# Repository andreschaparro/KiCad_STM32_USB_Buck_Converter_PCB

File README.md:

# KiCad STM32 + USB + Buck Converter PCB Design and JLCPCB Assembly

## Links

- [Fabricante de PCB](https://jlcpcb.com/).
- [Componentes](https://jlcpcb.com/parts).
- [Microcontrolador STM32 F4](https://jlcpcb.com/partdetail/Stmicroelectronics-STM32F405RGT6/C15742).
- [Conversor Buck](https://jlcpcb.com/partdetail/Monolithic_PowerSystems-MP2359DJ_LFZ/C14259).
- [Protección ESD para el USB](https://jlcpcb.com/partdetail/Stmicroelectronics-USBLC62SC6/C7519).
- [Cristal 16Mhz](https://jlcpcb.com/partdetail/Yxc_CrystalOscillators-X322516MLB4SI/C13738).
- [Protección Polaridad Inversa](https://jlcpcb.com/partdetail/Alpha_OmegaSemicon-AO3401A/C15127).
- [Ferrite para Conversores Buck](https://jlcpcb.com/partdetail/Sunlord-GZ2012D601TF/C1017).
- [Diodo Schottky recomendado para Conversores Buck](https://jlcpcb.com/partdetail/mdd_microdiode_semiconductor-B5819W/C64885).
- [Inductor de potencia para Conversores Buck](https://jlcpcb.com/partdetail/Sunlord-MWSA0503S100MT/C408412).

❗Minimizar el uso de extended parts y usar las basic para minimizar el costo del PCB.

## STM32CubeIDE

📝En lo posible, colocar los buses de comunicación en distintos laterales del microcontrolador. Y si no se puede, colocarlos lo mas separados que se pueda dentro del mismo lateral.

❗En la imagen, se ve una mala ubicación para la USART1 porque queda muy cerca del USB_FS. Para solucionar el problema, utilizar la USART3 que esta en otro lateral.

## Opciones para interconectar VDD con VDDA

## Cortex Debug Connector (10-pins, 0.05")

## Apilado estándar de 4 capas de JLCPCB

## Reglas de diseño JLCPCB

[Fabricante de PCB](https://jlcpcb.com/capabilities/pcb-capabilities).

## Pasos para armar el Layout

📝Trabajar con una grilla de 1mm o 0,25mm.

❗Si hay restricciones mecánicas, primero dibujar el borde de la placa y posicionar agujeros de montaje.

1. Colocar el microcontrolador.
2. Separar los componentes en grupos funcionales.
3. Colocar los capacitores de desacople de 100n lo mas cerca posible del microcontrolador.
4. Colocar el filtro de conexión entre VDD y VDDA lo mas cerca posible del microcontrolador.
5. Colocar los capacitores de VCAP_1 y VCAP_2 lo mas cerca posible del microcontrolador.
6. Colocar el circuito del cristal lo mas cerca posible del microcontrolador.
7. Colocar el capacitor de desacople de 4u7 o 10u cerca del capacitor de 100n que está más alejado de la salida del regulador Buck.

📝Medir distancias con la regla.

8. Colocar elementos del BOOT0.
9. Colocar el led de status.
10. Colocar el conector USB (con su protección ESD lo más cerca posible).
11. Colocar el conector de la UART.
12. Colocar el conector I2C y sus resistencia (más cerca del host que del conector).
13. Colocar los conectores de Debug y +12V.
14. Colocar todos los componentes del circuito de alimentación dentro de un área pequeña.

📝Utilizar el layout sugerido en la hoja de datos del conversor Buck.
📝Si no hay layout sugerido, los componentes de la red de realimentación deben estar cerca del conversor Buck.
📝Si no hay layout sugerido, los componentes de la red de filtrado deben estar cercanos entre sí y del conversor Buck.
📝Si hubiese señales análogicas, deberían estar bastante separadas del área del conversor Buck.

15. Colocar leds indicadores de alimentación.
16. Colocar los agujeros de montaje.
17. Dibujar el borde de la placa.
18. Ajustar conectores y otros elementos utilizando la perspectiva 3D de KiCad.

❗JLCPCB no utiliza las capas F.Fab y B.Fab. Por lo que se puede, enviar la númeración de componetes al F.Fab para ahorrar espacio.

## Pasos para el ruteo

📝Un ancho de pista de 0,3mm es práctico para hacer conexiones directa con el microcontrolador.

1. Capacitores de desacople.
2. La pista de HSE_IN debe pasar por el medio del cristal.

📝Corregir la posición vertical del cristal manualmente.

3. Todas las conexiones del circuito del cristal deben realizarse en el top layer.
4. Las pistas I2C_SDA e I2C_SDL deben separarse al menos 2 a 3 veces su ancho, y lo mas cerca posible del microcontrolador para evitar Crosstalk.
5. Las pistas TX y RX de una USART deben separarse con el mismo criterio que las de I2C.
6. Las pistas de Debug son de baja frecuencia.

❗Las pistas de baja frecuencia se pueden pasar por el bottom layer mediante vías y deben ser lo mas cortas posibles.

7. Para las pistas del circuito de alimentación, se pueden utilizar zonas de cobre o pistas gruesas.

📝La herramienta de cálculo de KiCad permite estimar la corriente que puede circular por una pista.

8. Las pistas USB son un par diferencial con impedancia controlada de 90.

📝Utilizar la herramienta [JLCPCB Impedance Calculator](https://jlcpcb.com/pcb-impedance-calculator) no la de KiCad.

9. La pista de BOOT0 es de baja frecuencia.
10. Realizar las conexiones con los planos de GND y +3.3V con vías de 0,8mm/0,4mm.

❗Las vías deben colocarse lo mas cerca posible sin tocar los pads para minimizar la resistencia e inductancia parásita.

📝Puede que haga falta más de una vía en función de la corriente.

❗Para la conexión entre VDD y VDDA poner al menos 2 vías para minimizar la resistencia e inductancia parásita.

❗Conectar las vías a los pads con trazos cortos y anchos (0,5mm o más).

❗En el regulador Buck utilizar al menos 2 vías por pad. Excepto, en el inductor donde conviene que tenga al menos 4.

❗En el GND del USB poner al menos 4 vías.

11. Agregar serigrafía:

- Función de los conectores.
- Función de los leds.
- Pin positivo de diodos y capacitores.
- Pin número 1 de los circuitos integrados.
- Nombre de la placa.
- Logo.

## Manufactura

1. Agregar el texto `JLCJLCJLCJLC` en el layer F.Silkscreen.

📝[How to mark on PCB?](https://jlcpcb.com/help/article/How-to-remove-order-number-from-your-PCB)

2. Agregar 3 o 4 tooling holes.

❗Son circulos de radio 0,576mm hechos en el layer Edge.Cuts.

❗Los mismos deben hubicarse en esquinas opuestas de la placa y lo más apartados uno del otro.

📝[How to add tooling holes for PCB assembly order](https://jlcpcb.com/help/article/How-to-add-tooling-holes-for-PCB-assembly-order)

3. Generar los gerbers.

4. Generar los drill files.
5. Comprimir los gerbers junto a los drill files.

📝[How to Prepare Gerber Files Before Placing Orders?](https://jlcpcb.com/help/article/gerber-files-preparation)

📝[How to generate Gerber and Drill files in KiCAD 8?](https://jlcpcb.com/help/article/how-to-generate-gerber-and-drill-files-in-kicad-8)

6. Generar los pick and place files.

7. Modificar el nombre de las columnas de los pick and place files.

8. Abrir el editor de esquemas y agregarle a los símbolos un campo llamado `JLCPCB Part #`.
9. Ingresar el `JLCPCB Part #` de cada componente.

❗Por el momento JLCPCB no ofrece componentes THT. Los mismos, deberán ser comprados por [LCSC](https://www.lcsc.com/) y soldados manualmente.

10. Instalar la extensión `JLC PCB abrication Toolkit` de KiCad.
11. Abrir el editor de placas y generar el BOM.

❗Con esta extensión se crea una carpeta llamada production con todos los archivos para la producción y dentro de ellos el BOM.

📝[Pick & Place File for PCB Assembly](https://jlcpcb.com/help/article/pick-place-file-for-pcb-assembly).

📝[Bill of Materials(BOM) File for PCB Assembly](https://jlcpcb.com/help/article/bill-of-materials-for-pcb-assembly)

📝[How to generate the BOM and Centroid file from KiCAD](https://jlcpcb.com/help/article/How-to-generate-the-BOM-and-Centroid-file-from-KiCAD).

12. Crear una cuenta en la página del fabricante.
13. Cargar los archivos y verificar la orientación de los componentes.

❗En la imagen se ve que hay que rotar: U2 -90°, U1 -180°, Q1 -180°, U3 -90°.

📝Cuando se rota un componente, un ángulo positivo es en contra de las agujas del reloj. Y un ángulo negativo en el sentido de las agujas del reloj.

14. Corregir la orientación de los componentes en los pick and place files.
15. Repetir el paso 12.

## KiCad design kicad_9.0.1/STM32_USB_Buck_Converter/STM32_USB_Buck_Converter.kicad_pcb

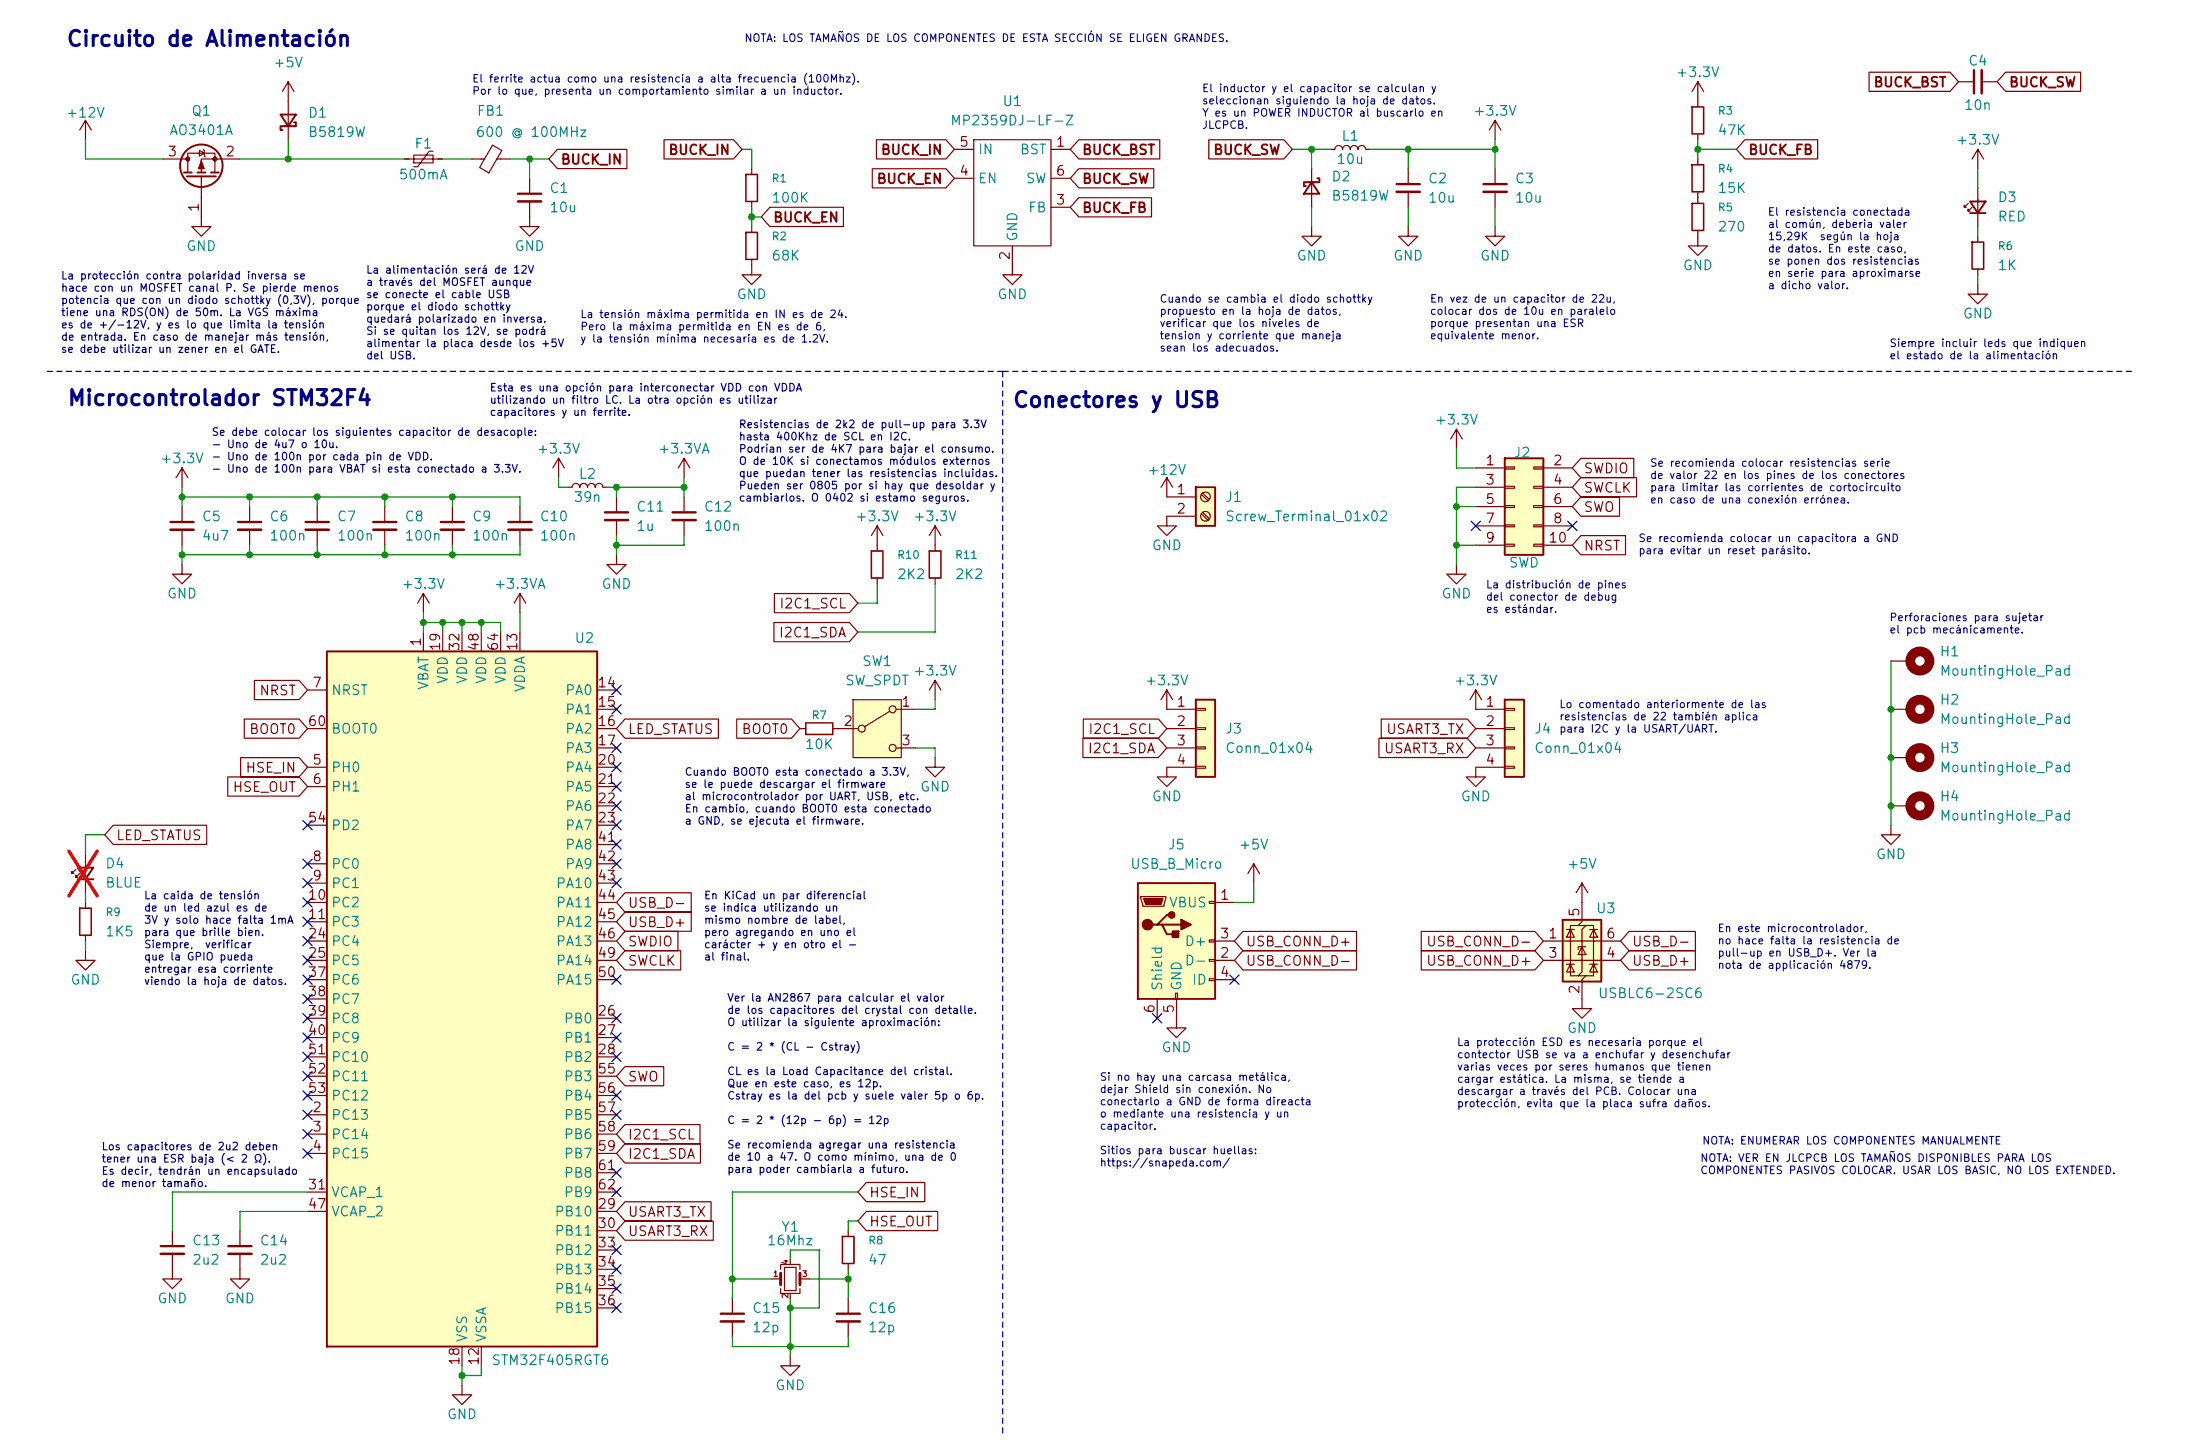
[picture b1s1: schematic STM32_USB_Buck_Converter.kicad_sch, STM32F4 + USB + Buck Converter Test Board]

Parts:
C1, C2, C3: 10u; C_1206_3216Metric; JLCPCB Part # C13585
C4: 10n; C_0603_1608Metric; JLCPCB Part # C57112
C5: 4u7; C_0603_1608Metric; JLCPCB Part # C19666
C6, C7, C8, C9, C10, C12: 100n; C_0402_1005Metric; JLCPCB Part # C1525
C11: 1u; C_0402_1005Metric; JLCPCB Part # C52923
C13, C14: 2u2; C_0603_1608Metric; JLCPCB Part # C15195
C15, C16: 12p; C_0402_1005Metric; JLCPCB Part # C1547
D1, D2: B5819W; D_SOD-123; JLCPCB Part # C8598
D3: RED; LED_0603_1608Metric; JLCPCB Part # C2286
D4: BLUE; LED_0603_1608Metric; JLCPCB Part # C72041; not fitted
F1: 500mA; Fuse_1206_3216Metric; JLCPCB Part # C369159
FB1: 600 @ 100MHz; L_0805_2012Metric; JLCPCB Part # C1017
H1, H2, H3, H4: MountingHole_Pad; MountingHole_4.3mm_M4_Pad_Via
J1: Screw_Terminal_01x02; TerminalBlock_Phoenix_PT-1,5-2-3.5-H_1x02_P3.50mm_Horizontal
J2: SWD; PinHeader_2x05_P1.27mm_Vertical_SMD
J3, J4: Conn_01x04; Molex_PicoBlade_53048-0410_1x04_P1.25mm_Horizontal
J5: USB_B_Micro
L1: 10u; L_Sunlord_MWSA0518S; JLCPCB Part # C139506
L2: 39n; L_0402_1005Metric; JLCPCB Part # C26443
Q1: AO3401A; SOT-23; JLCPCB Part # C15127
R1: 100K; R_0603_1608Metric; JLCPCB Part # C25803
R2: 68K; R_0603_1608Metric; JLCPCB Part # C23231
R3: 47K; R_0603_1608Metric; JLCPCB Part # C25819
R4: 15K; R_0603_1608Metric; JLCPCB Part # C22809
R5: 270; R_0603_1608Metric; JLCPCB Part # C22966
R6: 1K; R_0603_1608Metric; JLCPCB Part # C21190
R7: 10K; R_0402_1005Metric; JLCPCB Part # C25744
R8: 47; R_0402_1005Metric; JLCPCB Part # C25118
R9: 1K5; R_0603_1608Metric; JLCPCB Part # C22843
R10, R11: 2K2; R_0402_1005Metric; JLCPCB Part # C4190
SW1: SW_SPDT; SW_SPDT_PCM12
U1: MP2359DJ-LF-Z; SOT-23-6; JLCPCB Part # C14259
U2: STM32F405RGT6; LQFP-64_10x10mm_P0.5mm; JLCPCB Part # C15742
U3: USBLC6-2SC6; SOT-23-6; JLCPCB Part # C7519
Y1: 16Mhz; Crystal_SMD_3225-4Pin_3.2x2.5mm; JLCPCB Part # C13738

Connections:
+3.3V: C2.1, C3.1, C5.1, C6.1, C7.1, C8.1, C9.1, C10.1, D3.2 (A), J2.1, J3.1, J4.1, L1.2, L2.1, R3.1, R10.1, R11.1, SW1.1 (A), U2.1 (VBAT), U2.19 (VDD), U2.32 (VDD), U2.48 (VDD), U2.64 (VDD)
+3.3VA: C11.1, C12.1, L2.2, U2.13 (VDDA)
+5V: D1.2 (A), J5.1 (VBUS), U3.5 (VBUS)
+12V: J1.1, Q1.3 (D)
BOOT0: R7.1, U2.60 (BOOT0)
BUCK_BST: C4.1, U1.1 (BST)
BUCK_EN: R1.2, R2.1, U1.4 (EN)
BUCK_FB: R3.2, R4.1, U1.3 (FB)
BUCK_IN: C1.1, FB1.2, R1.1, U1.5 (IN)
BUCK_SW: C4.2, D2.1 (K), L1.1, U1.6 (SW)
GND: C1.2, C2.2, C3.2, C5.2, C6.2, C7.2, C8.2, C9.2, C10.2, C11.2, C12.2, C13.2, C14.2, C15.2, C16.2, D2.2 (A), H1.1, H2.1, H3.1, H4.1, J1.2, J2.3, J2.5, J2.9, J3.4, J4.4, J5.5 (GND), Q1.1 (G), R2.2, R5.2, R6.2, R9.2, SW1.3 (C), U1.2 (GND), U2.12 (VSSA), U2.18 (VSS), U2.63 (VSS), U3.2 (GND), Y1.2, Y1.4
HSE_IN: C15.1, U2.5 (PH0), Y1.1
HSE_OUT: R8.1, U2.6 (PH1)
I2C1_SCL: J3.2, R10.2, U2.58 (PB6)
I2C1_SDA: J3.3, R11.2, U2.59 (PB7)
LED_STATUS: D4.2 (A), U2.16 (PA2)
NRST: J2.10, U2.7 (NRST)
unnamed: C16.1, R8.2, Y1.3
unnamed: D1.1 (K), F1.1, Q1.2 (S)
unnamed: D3.1 (K), R6.1
unnamed: D4.1 (K), R9.1
unnamed: F1.2, FB1.1
unnamed: R4.2, R5.1
unnamed: R7.2, SW1.2 (B)
unnamed: C13.1, U2.31 (VCAP_1)
unnamed: C14.1, U2.47 (VCAP_2)
SWCLK: J2.4, U2.49 (PA14)
SWDIO: J2.2, U2.46 (PA13)
SWO: J2.6, U2.55 (PB3)
USART3_RX: J4.3, U2.30 (PB11)
USART3_TX: J4.2, U2.29 (PB10)
USB_CONN_D+: J5.3 (D+), U3.3 (I/O2)
USB_CONN_D-: J5.2 (D-), U3.1 (I/O1)
USB_D+: U2.45 (PA12), U3.4 (I/O2)
USB_D-: U2.44 (PA11), U3.6 (I/O1)

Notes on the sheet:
En este microcontrolador, no hace falta la resistencia de pull-up en USB_D+. Ver la nota de applicación 4879.
En KiCad un par diferencial se indica utilizando un mismo nombre de label, pero agregando en uno el carácter + y en otro el - al final.
Resistencias de 2k2 de pull-up para 3.3V hasta 400Khz de SCL en I2C. Podrían ser de 4K7 para bajar el consumo. O de 10K si conectamos módulos externos que puedan tener las resistencias incluidas. Pueden ser 0805 por si hay que desoldar y cambiarlos. O 0402 si estamo seguros.
Se recomienda colocar resistencias serie de valor 22 en los pines de los conectores para limitar las corrientes de cortocircuito en caso de una conexión errónea.
La protección contra polaridad inversa se hace con un MOSFET canal P. Se pierde menos potencia que con un diodo schottky (0,3V), porque tiene una RDS(ON) de 50m. La VGS máxima es de +/-12V, y es lo que limita la tensión de entrada. En caso de manejar más tensión, se debe utilizar un zener en el GAT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
La tensión máxima permitida en IN es de 24. Pero la máxima permitida en EN es de 6, y la tensión mínima necesaria es de 1.2V.
Los capacitores de 2u2 deben tener una ESR baja (< 2 Ω). Es decir, tendrán un encapsulado de menor tamaño.
NOTA: LOS TAMAÑOS DE LOS COMPONENTES DE ESTA SECCIÓN SE ELIGEN GRANDES.
Se recomienda colocar un capacitora a GND para evitar un reset parásito.
Esta es una opción para interconectar VDD con VDDA utilizando un filtro LC. La otra opción es utilizar capacitores y un ferrite.
Cuando BOOT0 esta conectado a 3.3V, se le puede descargar el firmware al microcontrolador por UART, USB, etc. En cambio, cuando BOOT0 esta conectado a GND, se ejecuta el firmware.
La alimentación será de 12V a través del MOSFET aunque se conecte el cable USB porque el diodo schottky quedará polarizado en inversa. Si se quitan los 12V, se podrá alimentar la placa desde los +5V del USB.
Ver la AN2867 para calcular el valor de los capacitores del crystal con detalle. O utilizar la siguiente aproximación: C = 2 * (CL - Cstray) CL es la Load Capacitance del cristal. Que en este caso, es 12p. Cstray es la del pcb y suele valer 5p o 6p. C = 2 * (12p - 6p) = 12p Se recomienda agregar un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
Perforaciones para sujetar el pcb mecánicamente.
El resistencia conectada al común, deberia valer 15,29K según la hoja de datos. En este caso, se ponen dos resistencias en serie para aproximarse a dicho valor.
La protección ESD es necesaria porque el contector USB se va a enchufar y desenchufar varias veces por seres humanos que tienen cargar estática. La misma, se tiende a descargar a través del PCB. Colocar una protección, evita que la placa sufra daños.
NOTA: ENUMERAR LOS COMPONENTES MANUALMENTE
Se debe colocar los siguientes capacitor de desacople: - Uno de 4u7 o 10u. - Uno de 100n por cada pin de VDD. - Uno de 100n para VBAT si esta conectado a 3.3V.
La distribución de pines del conector de debug es estándar.
Lo comentado anteriormente de las resistencias de 22 también aplica para I2C y la USART/UART.
Conectores y USB
NOTA: VER EN JLCPCB LOS TAMAÑOS DISPONIBLES PARA LOS COMPONENTES PASIVOS COLOCAR. USAR LOS BASIC, NO LOS EXTENDED.
Cuando se cambia el diodo schottky propuesto en la hoja de datos, verificar que los niveles de tension y corriente que maneja sean los adecuados.
La caida de tensión de un led azul es de 3V y solo hace falta 1mA para que brille bien. Siempre, verificar que la GPIO pueda entregar esa corriente viendo la hoja de datos.
El inductor y el capacitor se calculan y seleccionan siguiendo la hoja de datos. Y es un POWER INDUCTOR al buscarlo en JLCPCB.
Siempre incluir leds que indiquen el estado de la alimentación
Circuito de Alimentación
El ferrite actua como una resistencia a alta frecuencia (100Mhz). Por lo que, presenta un comportamiento similar a un inductor.
En vez de un capacitor de 22u, colocar dos de 10u en paralelo porque presentan una ESR equivalente menor.
Microcontrolador STM32F4
Si no hay una carcasa metálica, dejar Shield sin conexión. No conectarlo a GND de forma direacta o mediante una resistencia y un capacitor. Sitios para buscar huellas: https://snapeda.com/

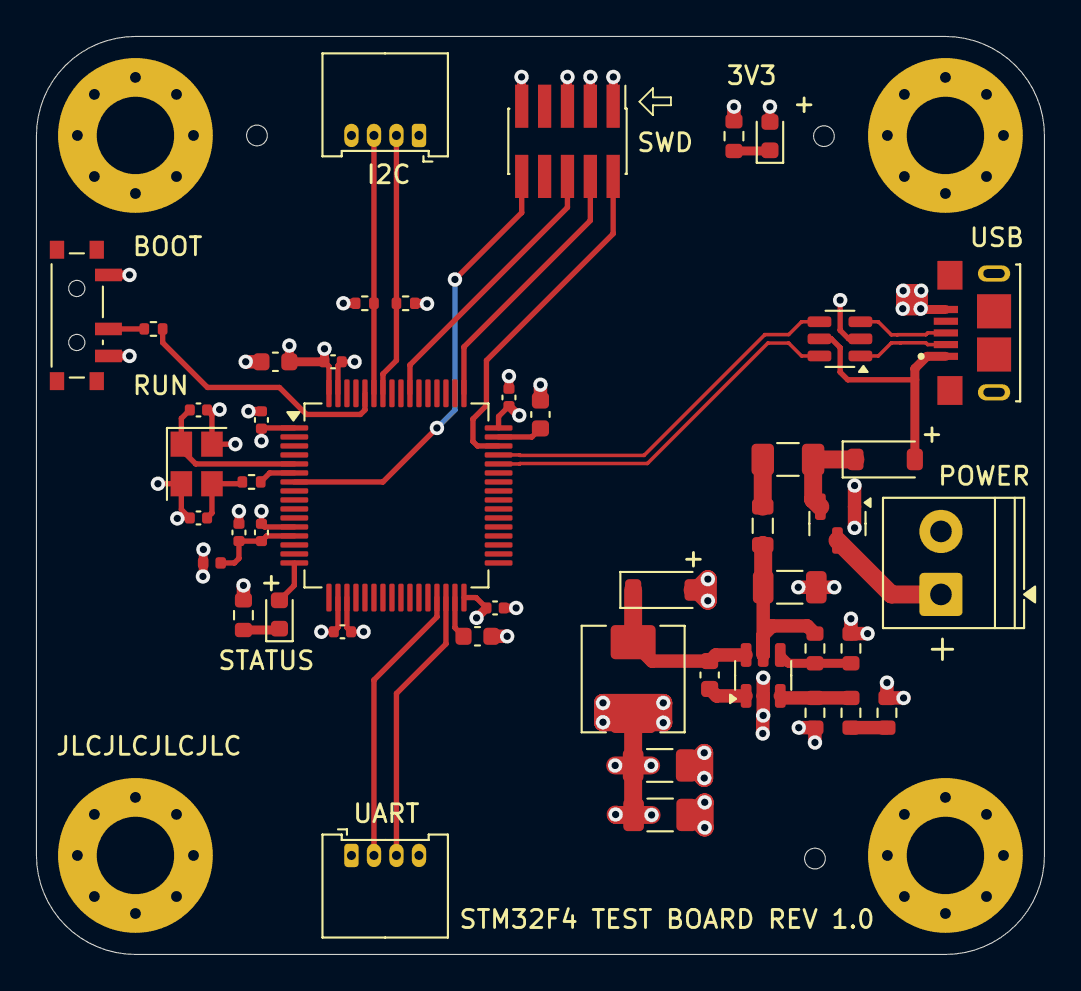
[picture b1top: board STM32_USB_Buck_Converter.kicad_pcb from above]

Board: 4 copper layers, 56.0 x 51.0 mm, 50 parts (0 on the bottom side), 35 nets.

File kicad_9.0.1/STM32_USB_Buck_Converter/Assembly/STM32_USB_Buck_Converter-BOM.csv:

Designator,Footprint,Quantity,Value,LCSC Part #
"C1, C2, C3",1206,3,10u,
"C10, C12, C6, C7, C8, C9",0402,6,100n,
C11,0402,1,1u,
"C13, C14",0603,2,2u2,
"C15, C16",0402,2,12p,
C4,0603,1,10n,
C5,0603,1,4u7,
"D1, D2",D_SOD-123,2,B5819W,
D3,0603,1,RED,
D4,0603,1,BLUE,
F1,1206,1,250mA,
FB1,0805,1,600 @ 100MHz,
J1,"TerminalBlock_Phoenix_PT-1,5-2-3.5-H_1x02_P3.50mm_Horizontal",1,Screw_Terminal_01x02,
J2,PinHeader_2x05_P1.27mm_Vertical_SMD,1,SWD,
"J3, J4",Molex_PicoBlade_53048-0410_1x04_P1.25mm_Horizontal,2,Conn_01x04,
J5,USB_B_Micro,1,USB_B_Micro,
L1,L_Sunlord_MWSA0518S,1,10u,
L2,0402,1,39n,
Q1,SOT-23,1,AO3401A,
R1,0603,1,100K,
"R10, R11",0402,2,2K2,
R2,0603,1,68K,
R3,0603,1,47K,
R4,0603,1,15K,
R5,0603,1,270,
R6,0603,1,1K,
R7,0402,1,10K,
R8,0402,1,47,
R9,0603,1,1K5,
SW1,SW_SPDT_PCM12,1,SW_SPDT,
U1,SOT-23-6,1,MP2359DJ-LF-Z,
U2,LQFP-64_10x10mm_P0.5mm,1,STM32F405RGT6,
U3,SOT-23-6,1,USBLC6-2SC6,
Y1,Crystal_SMD_3225-4Pin_3.2x2.5mm,1,16Mhz,

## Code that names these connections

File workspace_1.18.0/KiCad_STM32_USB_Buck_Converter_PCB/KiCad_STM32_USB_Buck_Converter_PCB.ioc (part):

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Mcu.Name=STM32F405RGTx
Mcu.Package=LQFP64
Mcu.UserName=STM32F405RGTx
PA11.Mode=Device_Only
PA11.Signal=USB_OTG_FS_DM
PA12.Mode=Device_Only
PA12.Signal=USB_OTG_FS_DP
PA13.Mode=Trace_Asynchronous_SW
PA13.Signal=SYS_JTMS-SWDIO
PA14.Mode=Trace_Asynchronous_SW
PA14.Signal=SYS_JTCK-SWCLK
PA2.GPIOParameters=GPIO_Label
PA2.GPIO_Label=LED_STATUS
PA2.Signal=GPIO_Output
PB10.Mode=Asynchronous
PB10.Signal=USART3_TX
PB11.Mode=Asynchronous
PB11.Signal=USART3_RX
PB3.Mode=Trace_Asynchronous_SW
PB3.Signal=SYS_JTDO-SWO
PB6.Mode=I2C
PB6.Signal=I2C1_SCL
PB7.Mode=I2C
PB7.Signal=I2C1_SDA
PH0-OSC_IN.Mode=HSE-External-Oscillator
PH0-OSC_IN.Signal=RCC_OSC_IN
PH1-OSC_OUT.Mode=HSE-External-Oscillator
PH1-OSC_OUT.Signal=RCC_OSC_OUT
RCC.HSE_VALUE=25000000
RCC.SYSCLKFreq_VALUE=16000000
board=custom

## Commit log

2025-04-24 Finalizado
2025-04-25 Archivos Pick and Place Corregidos
2025-04-25 .gitignore corregido
2025-04-25 .gitignore final
2025-04-25 version final
2025-04-25 archivos de stm32cubeide corregidos
2025-04-25 .metadata removida
2025-04-25 csv agregados
